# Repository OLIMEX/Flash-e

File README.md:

# Flash-e
External eMMC and SPI Flash module

https://www.olimex.com/Products/OLinuXino/Accessories/Flash-e32Gs16M/

## Licensee
* Hardware is released under CERN Open Hardware Licence Version 2 - Strongly Reciprocal
* Software is released under GPL V3 Licensee
* Documentation is released under CC BY-SA 4.0

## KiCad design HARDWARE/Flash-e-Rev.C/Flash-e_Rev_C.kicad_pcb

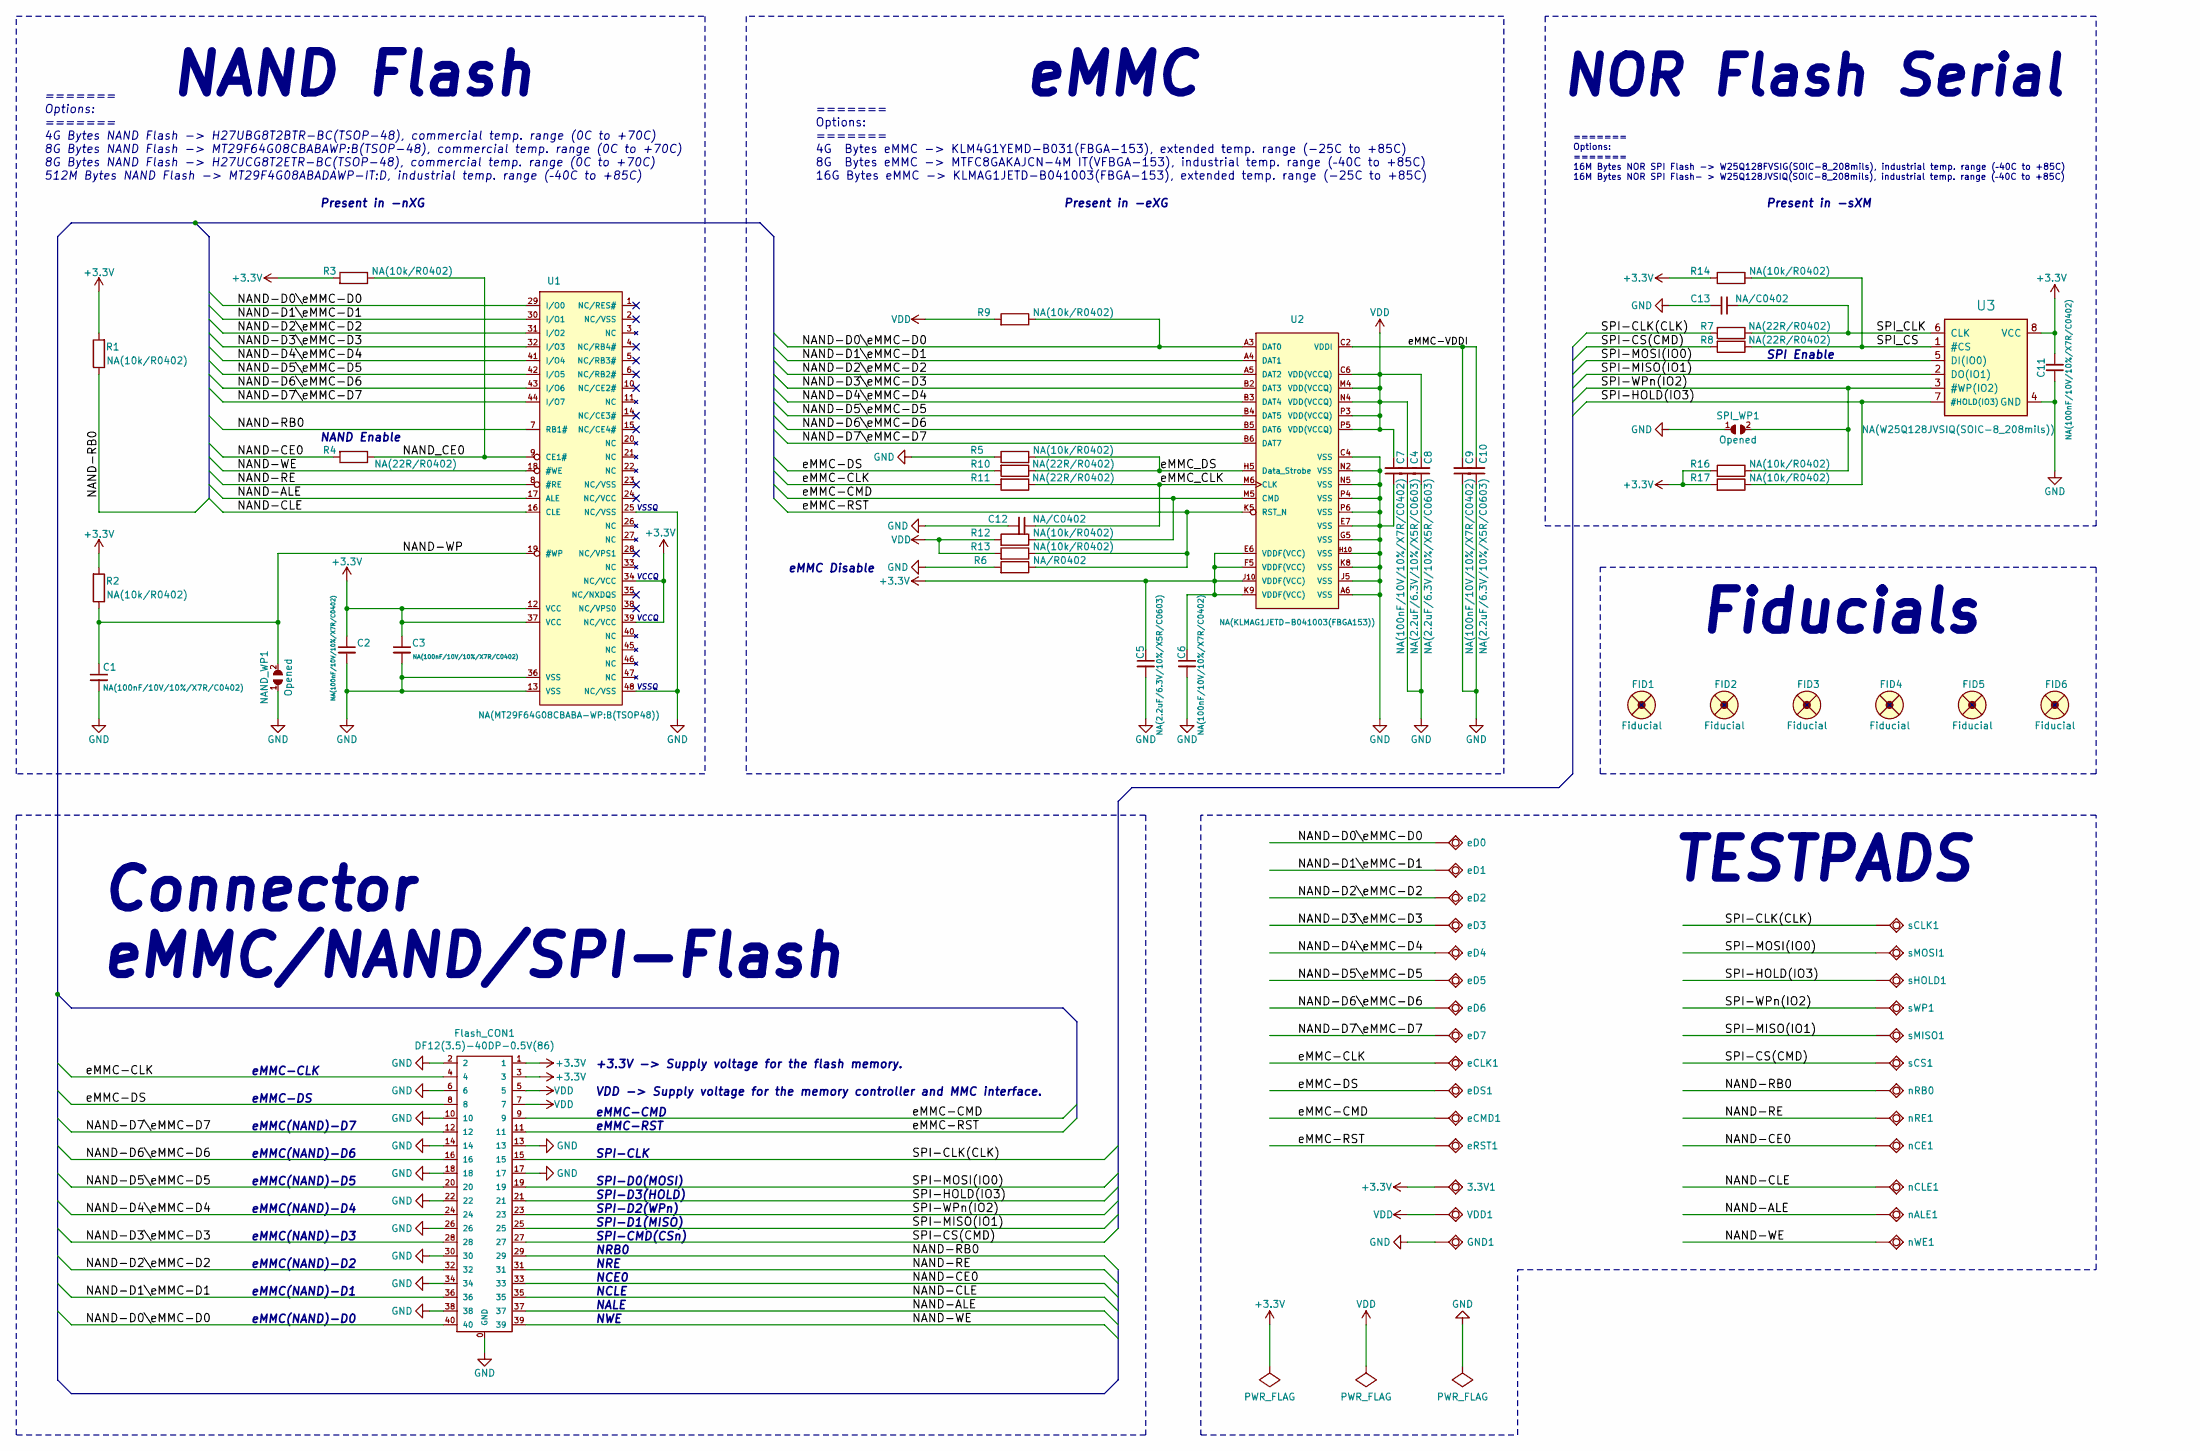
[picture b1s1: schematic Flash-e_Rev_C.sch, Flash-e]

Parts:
3.3V1: TESTPAD; TEST_PAD_0.6x0.9mm
C1, C2, C3, C6, C7, C9, C11: NA(100nF/10V/10%/X7R/C0402); C_0402_5MIL_DWS
C4, C5, C8, C10: NA(2.2uF/6.3V/10%/X5R/C0603); C_0603_5MIL_DWS
C12, C13: NA/C0402; C_0402_5MIL_DWS
FID1, FID2, FID3, FID4, FID5, FID6: Fiducial; Fiducial1x3
Flash_CON1: DF12(3.5)-40DP-0.5V(86); DF12(3.5)-40DP-0.5V(86)---(CL0537-0032-4-86)-0.25mm_Cream
GND1: TESTPAD; TEST_PAD_0.6x0.9mm
NAND_WP1: Opened; SJ_1_SMALLER
R1, R2, R3, R5, R9, R12, R13, R14, R16, R17: NA(10k/R0402); R_0402_5MIL_DWS
R4, R7, R8, R10, R11: NA(22R/R0402); R_0402_5MIL_DWS
R6: NA/R0402; R_0402_5MIL_DWS
SPI_WP1: Opened; SJ_1_SMALLER
U1: NA(MT29F64G08CBABA-WP:B(TSOP48)); TSOP48
U2: NA(KLMAG1JETD-B041003(FBGA153)); FBGA153_Pitch-0.5mm_Ball-0.25mm_Dimensions-11.50x13.00x0.80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
U3: NA(W25Q128JVSIQ(SOIC-8_208mils)); SO-8_208mil
VDD1: TESTPAD; TEST_PAD_0.6x0.9mm
eCLK1: TESTPAD; TEST_PAD_0.6x0.9mm
eCMD1: TESTPAD; TEST_PAD_0.6x0.9mm
eD0, eD1, eD2, eD3, eD4, eD5, eD6, eD7: TESTPAD; TEST_PAD_0.6x0.9mm
eDS1: TESTPAD; TEST_PAD_0.6x0.9mm
eRST1: TESTPAD; TEST_PAD_0.6x0.9mm
nALE1: TESTPAD; TEST_PAD_0.6x0.9mm
nCE1: TESTPAD; TEST_PAD_0.6x0.9mm
nCLE1: TESTPAD; TEST_PAD_0.6x0.9mm
nRB0: TESTPAD; TEST_PAD_0.6x0.9mm
nRE1: TESTPAD; TEST_PAD_0.6x0.9mm
nWE1: TESTPAD; TEST_PAD_0.6x0.9mm
sCLK1: TESTPAD; TEST_PAD_0.6x0.9mm
sCS1: TESTPAD; TEST_PAD_0.6x0.9mm
sHOLD1: TESTPAD; TEST_PAD_0.6x0.9mm
sMISO1: TESTPAD; TEST_PAD_0.6x0.9mm
sMOSI1: TESTPAD; TEST_PAD_0.6x0.9mm
sWP1: TESTPAD; TEST_PAD_0.6x0.9mm

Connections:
+3V3: 3.3V1.1, C2.1, C3.1, C5.1, C6.1, C11.2, Flash_CON1.1, Flash_CON1.3, R1.2, R2.2, R3.2, R14.2, R16.2, R17.2, U1.12 (VCC), U1.34 (NC/VCC), U1.37 (VCC), U1.39 (NC/VCC), U2.E6 (VDDF(VCC)), U2.F5 (VDDF(VCC)), U2.J10 (VDDF(VCC)), U2.K9 (VDDF(VCC)), U3.8 (VCC)
/NAND-ALE: Flash_CON1.37, U1.17 (ALE), nALE1.1
/NAND-CE0: Flash_CON1.33, R4.2, nCE1.1
/NAND-CLE: Flash_CON1.35, U1.16 (CLE), nCLE1.1
/NAND-D0\eMMC-D0: Flash_CON1.40, R9.1, U1.29 (I/O0), U2.A3 (DAT0), eD0.1
/NAND-D1\eMMC-D1: Flash_CON1.36, U1.30 (I/O1), U2.A4 (DAT1), eD1.1
/NAND-D2\eMMC-D2: Flash_CON1.32, U1.31 (I/O2), U2.A5 (DAT2), eD2.1
/NAND-D3\eMMC-D3: Flash_CON1.28, U1.32 (I/O3), U2.B2 (DAT3), eD3.1
/NAND-D4\eMMC-D4: Flash_CON1.24, U1.41 (I/O4), U2.B3 (DAT4), eD4.1
/NAND-D5\eMMC-D5: Flash_CON1.20, U1.42 (I/O5), U2.B4 (DAT5), eD5.1
/NAND-D6\eMMC-D6: Flash_CON1.16, U1.43 (I/O6), U2.B5 (DAT6), eD6.1
/NAND-D7\eMMC-D7: Flash_CON1.12, U1.44 (I/O7), U2.B6 (DAT7), eD7.1
/NAND-RB0: Flash_CON1.29, R1.1, U1.7 (RB1#), nRB0.1
/NAND-RE: Flash_CON1.31, U1.8 (#RE), nRE1.1
/NAND-WE: Flash_CON1.39, U1.18 (#WE), nWE1.1
/NAND-WP: C1.1, NAND_WP1.2, R2.1, U1.19 (#WP)
/NAND_CE0: R3.1, R4.1, U1.9 (CE1#)
/SPI-CLK(CLK): Flash_CON1.15, R7.2, sCLK1.1
/SPI-CS(CMD): Flash_CON1.27, R8.2, sCS1.1
/SPI-HOLD(IO3): Flash_CON1.21, R17.1, U3.7 (#HOLD(IO3)), sHOLD1.1
/SPI-MISO(IO1): Flash_CON1.25, U3.2 (DO(IO1)), sMISO1.1
/SPI-MOSI(IO0): Flash_CON1.19, U3.5 (DI(IO0)), sMOSI1.1
/SPI-WPn(IO2): Flash_CON1.23, R16.1, SPI_WP1.2, U3.3 (#WP(IO2)), sWP1.1
/SPI_CLK: C13.1, R7.1, U3.6 (CLK)
/SPI_CS: R8.1, R14.1, U3.1 (#CS)
/eMMC-CLK: Flash_CON1.4, R11.2, eCLK1.1
/eMMC-CMD: Flash_CON1.9, R12.1, U2.M5 (CMD), eCMD1.1
/eMMC-DS: Flash_CON1.8, R10.2, eDS1.1
/eMMC-RST: Flash_CON1.11, R6.1, R13.1, U2.K5 (RST_N), eRST1.1
/eMMC-VDDI: C9.2, C10.2, U2.C2 (VDDI)
/eMMC_CLK: C12.1, R11.1, U2.M6 (CLK)
/eMMC_DS: R5.2, R10.1, U2.H5 (Data_Strobe)
GND: C1.2, C2.2, C3.2, C4.1, C5.2, C6.2, C7.1, C8.1, C9.1, C10.1, C11.1, C12.2, C13.2, Flash_CON1.0 (GND), Flash_CON1.2, Flash_CON1.6, Flash_CON1.10, Flash_CON1.13, Flash_CON1.14, Flash_CON1.17, Flash_CON1.18, Flash_CON1.22, Flash_CON1.26, Flash_CON1.30, Flash_CON1.34, Flash_CON1.38, GND1.1, NAND_WP1.1, R5.1, R6.2, SPI_WP1.1, U1.13 (VSS), U1.25 (NC/VSS), U1.36 (VSS), U1.48 (NC/VSS), U2.A6 (VSS), U2.C4 (VSS), U2.E7 (VSS), U2.G5 (VSS), U2.H10 (VSS), U2.J5 (VSS), U2.K8 (VSS), U2.N2 (VSS), U2.N5 (VSS), U2.P4 (VSS), U2.P6 (VSS), U3.4 (GND)
VDD: C4.2, C7.2, C8.2, Flash_CON1.5, Flash_CON1.7, R9.2, R12.2, R13.2, U2.C6 (VDD(VCCQ)), U2.M4 (VDD(VCCQ)), U2.N4 (VDD(VCCQ)), U2.P3 (VDD(VCCQ)), U2.P5 (VDD(VCCQ)), VDD1.1

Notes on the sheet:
NAND Flash
Present in -nXG
NOR Flash Serial
eMMC
Present in -eXG
Present in -sXM
======= Options: ======= 4G Bytes eMMC -> KLM4G1YEMD-B031(FBGA-153), extended temp. range (-25C to +85C) 8G Bytes eMMC -> MTFC8GAKAJCN-4M IT(VFBGA-153), industrial temp. range (–40C to +85C) 16G Bytes eMMC -> KLMAG1JETD-B041003(FBGA-153), extended temp. range (-25C to +85C)
eMMC(NAND)-D0
eMMC(NAND)-D1
eMMC(NAND)-D2
eMMC(NAND)-D3
eMMC-CLK
Connector eMMC/NAND/SPI-Flash
eMMC(NAND)-D5
eMMC(NAND)-D7
eMMC(NAND)-D6
eMMC-DS
eMMC(NAND)-D4
NAND Enable
eMMC Disable
SPI Enable
Fiducials
======= Options: ======= 4G Bytes NAND Flash -> H27UBG8T2BTR-BC(TSOP-48), commercial temp. range (0C to +70C) 8G Bytes NAND Flash -> MT29F64G08CBABAWP:B(TSOP-48), commercial temp. range (0C to +70C) 8G Bytes NAND Flash -> H27UCG8T2ETR-BC(TSOP-48), commercial temp. range (0C to +70C) 512M Bytes NAND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
eMMC-CMD
NRB0
NCE0
NWE
NRE
NALE
NCLE
SPI-CMD(CSn)
SPI-CLK
SPI-D3(HOLD)
SPI-D2(WPn)
SPI-D1(MISO)
SPI-D0(MOSI)
VDD -> Supply voltage for the memory controller and MMC interface.
+3.3V -> Supply voltage for the flash memory.
eMMC-RST
VSSQ

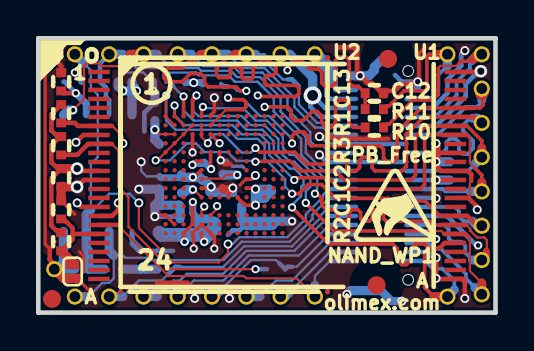
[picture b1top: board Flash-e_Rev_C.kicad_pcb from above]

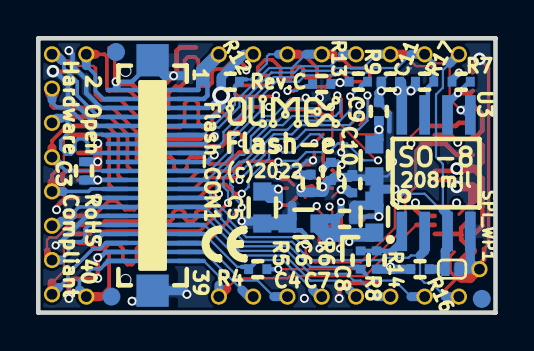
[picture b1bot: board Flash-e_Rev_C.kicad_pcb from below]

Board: 4 copper layers, 25.4 x 15.2 mm, 71 parts (28 on the bottom side), 34 nets.

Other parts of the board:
Logo_OLimeX: LOGO_OLIMEX_80
Sign_Antistatic: LOGO_ANTISTATIC_SMALL_4.5mmX2.8mm
Sign_CE_Small: CE_Sign_Small

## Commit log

2024-04-18 initial comit

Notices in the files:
HARDWARE/Flash-e-Rev.C/Flash-e_Rev_C.kicad_pcb:
(c)2022
